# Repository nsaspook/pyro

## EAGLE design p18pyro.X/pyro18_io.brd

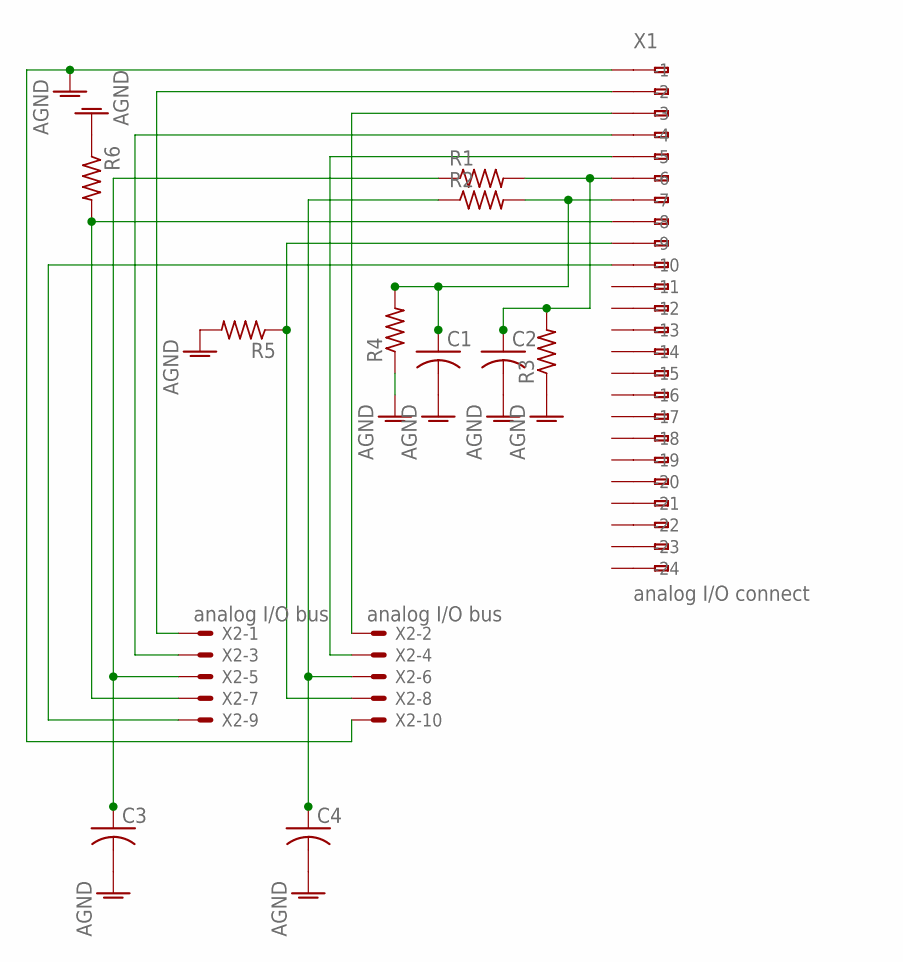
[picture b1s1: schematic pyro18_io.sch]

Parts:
C1, C2, C3, C4: C-US025-024X044; C025-024X044
R1, R2, R3, R4, R5, R6: R-US_0204/2V; 0204V
X1: analog I/O connect; 233-224
X2: analog I/O bus; 332-10

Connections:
AGND: C1.2, C2.2, C3.2, C4.2, R3.1, R4.1, R5.2, R6.1, X1.A1 (-1), X2.10
unnamed: C1.1, R2.2, R4.2, X1.A7 (-7)
unnamed: X1.A10 (-10), X2.9
unnamed: X1.A4 (-4), X2.3
unnamed: X1.A2 (-2), X2.1
unnamed: X1.A3 (-3), X2.2
unnamed: X1.A5 (-5), X2.4
unnamed: C3.1, R1.1, X2.5
unnamed: C4.1, R2.1, X2.6
unnamed: R6.2, X1.A8 (-8), X2.7
unnamed: R5.1, X1.A9 (-9), X2.8
unnamed: C2.1, R1.2, R3.2, X1.A6 (-6)

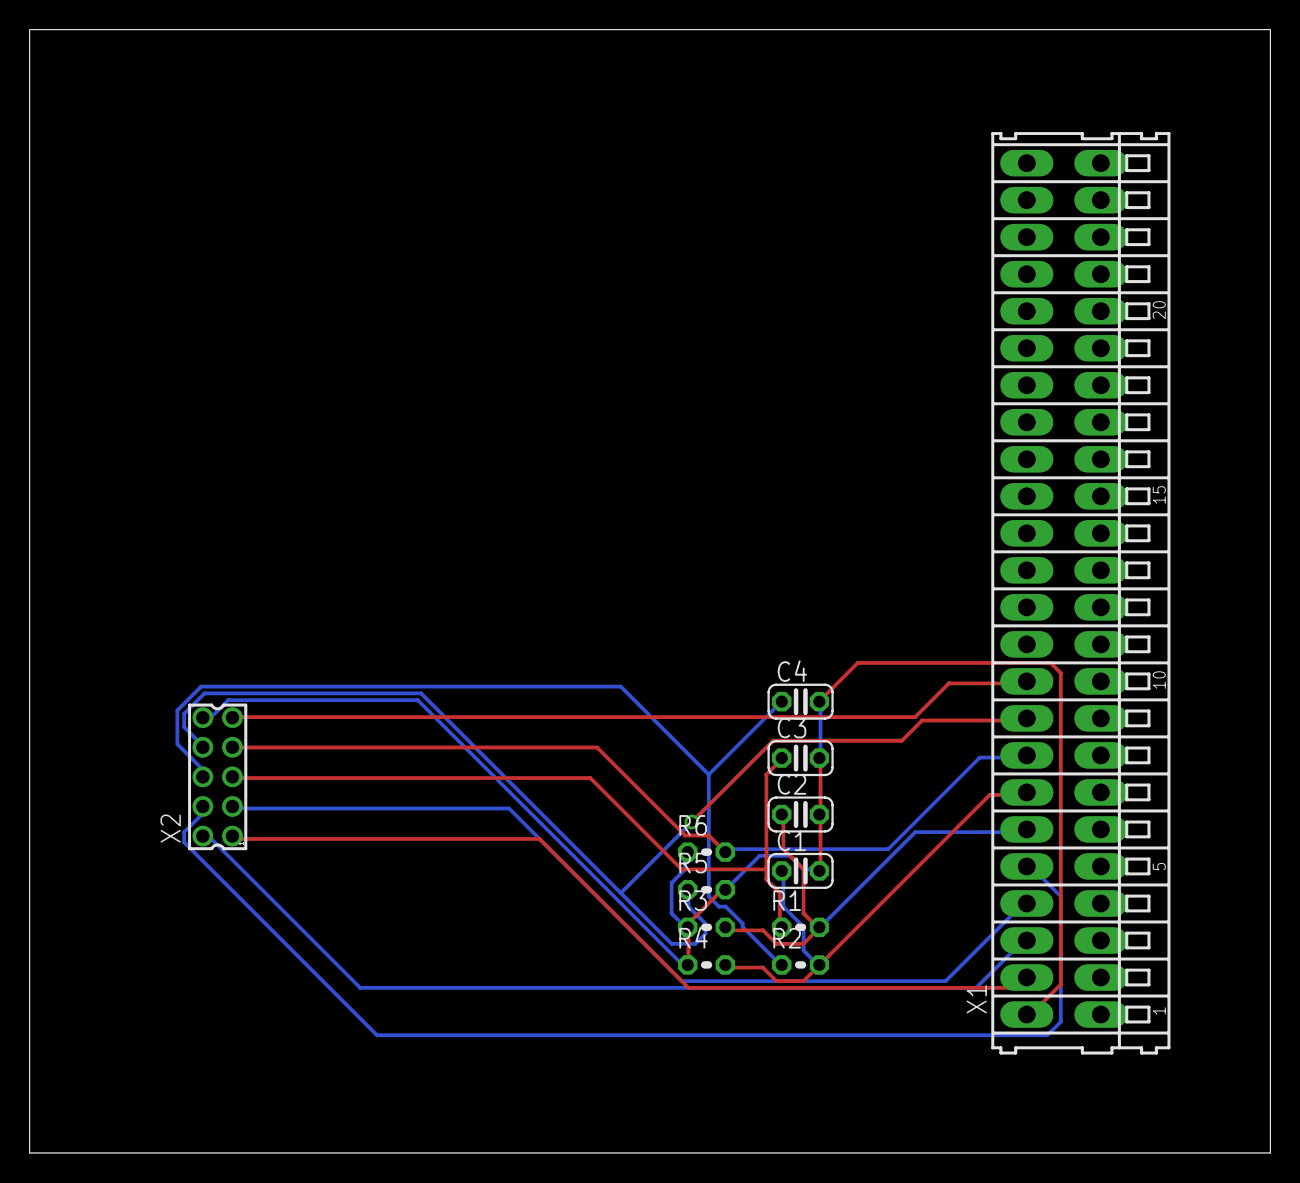
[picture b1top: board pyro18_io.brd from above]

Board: 2 copper layers, 83.8 x 75.9 mm, 12 parts (0 on the bottom side), 12 nets.

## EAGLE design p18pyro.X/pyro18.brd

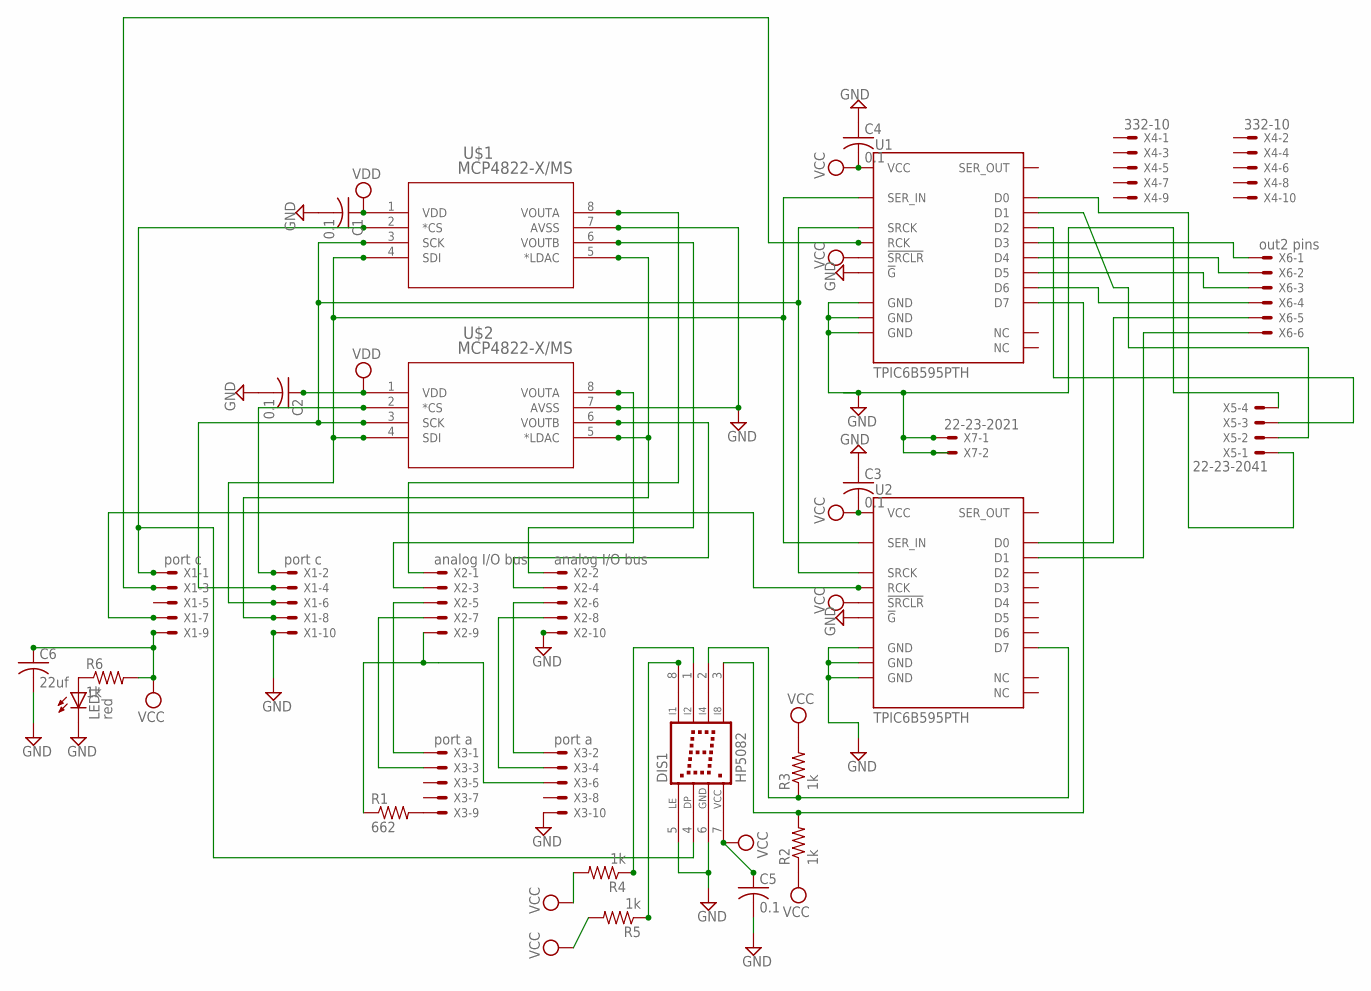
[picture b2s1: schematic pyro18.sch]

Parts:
C1, C2, C3, C4, C5: 0.1; C0805
C6: 22uf; C0805
DIS1: HP5082
LED1: red; LED3MM
R1: 662; 0207/2V
R2, R3, R4, R5, R6: 1k; 0207/2V
U1, U2: TPIC6B595PTH; DIL20
U$1, U$2: MCP4822-X/MS; MSOP8_MC
X1: port c; 332-10
X2: analog I/O bus; 332-10
X3: port a; 332-10
X4: 332-10
X5: 22-23-2041
X6: out2 pins; 22-23-2061
X7: 22-23-2021

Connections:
GND: C1.2, C2.2, C3.1, C4.1, C5.2, C6.2, DIS1.5 (LE), DIS1.6 (GND), LED1.K (C), U1.9 (!G), U1.10 (GND), U1.11 (GND), U1.19 (GND), U2.9 (!G), U2.10 (GND), U2.11 (GND), U2.19 (GND), U$1.7 (AVSS), U$2.7 (AVSS), X1.10, X2.10, X3.10, X5.4, X7.1, X7.2
unnamed: DIS1.4 (DP), U$1.2 (*CS), X1.1
unnamed: U$2.2 (*CS), X1.2
unnamed: U$1.5 (*LDAC), U$2.5 (*LDAC), X1.8
unnamed: U$1.8 (VOUTA), X2.1
unnamed: U1.13 (SRCK), U2.13 (SRCK), U$1.3 (SCK), U$2.3 (SCK), X1.4
unnamed: U1.4 (D0), X5.1
unnamed: U$1.6 (VOUTB), X2.2
unnamed: U1.3 (SER_IN), U2.3 (SER_IN), U$1.4 (SDI), U$2.4 (SDI), X1.6
unnamed: U$2.8 (VOUTA), X2.3
unnamed: U1.12 (RCK), X1.3
unnamed: U2.12 (RCK), X1.7
unnamed: U$2.6 (VOUTB), X2.4
unnamed: X2.5, X3.1
unnamed: X2.6, X3.2
unnamed: X2.7, X3.3
unnamed: X2.8, X3.4
unnamed: R1.1, X2.9, X3.6
unnamed: R1.2, X3.9
unnamed: DIS1.2 (I4), R3.1, U2.17 (D7)
unnamed: DIS1.3 (I8), R2.2, U1.17 (D7)
unnamed: U1.5 (D1), X5.2
unnamed: DIS1.8 (I1), R5.1
unnamed: DIS1.1 (I2), R4.1
unnamed: U1.6 (D2), X5.3
unnamed: U1.14 (D4), X6.2
unnamed: U1.7 (D3), X6.1
unnamed: U1.15 (D5), X6.3
unnamed: U1.16 (D6), X6.4
unnamed: U2.4 (D0), X6.5
unnamed: U2.5 (D1), X6.6
unnamed: LED1.A, R6.1
VCC: C3.2, C4.2, C5.1, C6.1, DIS1.7 (VCC), R2.1, R3.2, R4.2, R5.2, R6.2, U1.2 (VCC), U1.8 (!SRCLR), U2.2 (VCC), U2.8 (!SRCLR), X1.9
VDD: C1.1, C2.1, U$1.1 (VDD), U$2.1 (VDD)

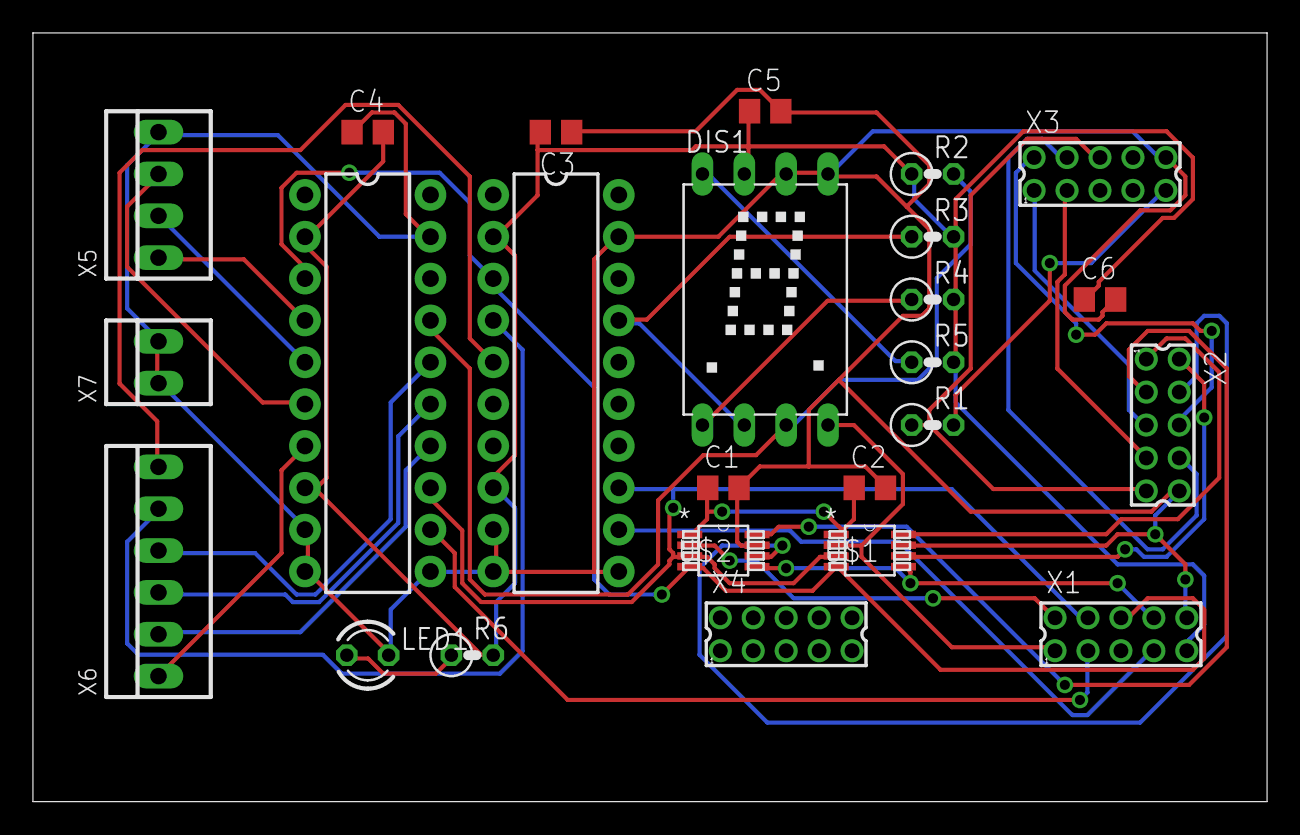
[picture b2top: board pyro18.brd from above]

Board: 2 copper layers, 74.9 x 46.7 mm, 25 parts (0 on the bottom side), 34 nets.

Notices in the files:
parts and their libraries:
SparkFun-DigitalIC: Licensing: Creative Commons ShareAlike 4.0 International - https://creativecommons.org/licenses/by-sa/4.0
